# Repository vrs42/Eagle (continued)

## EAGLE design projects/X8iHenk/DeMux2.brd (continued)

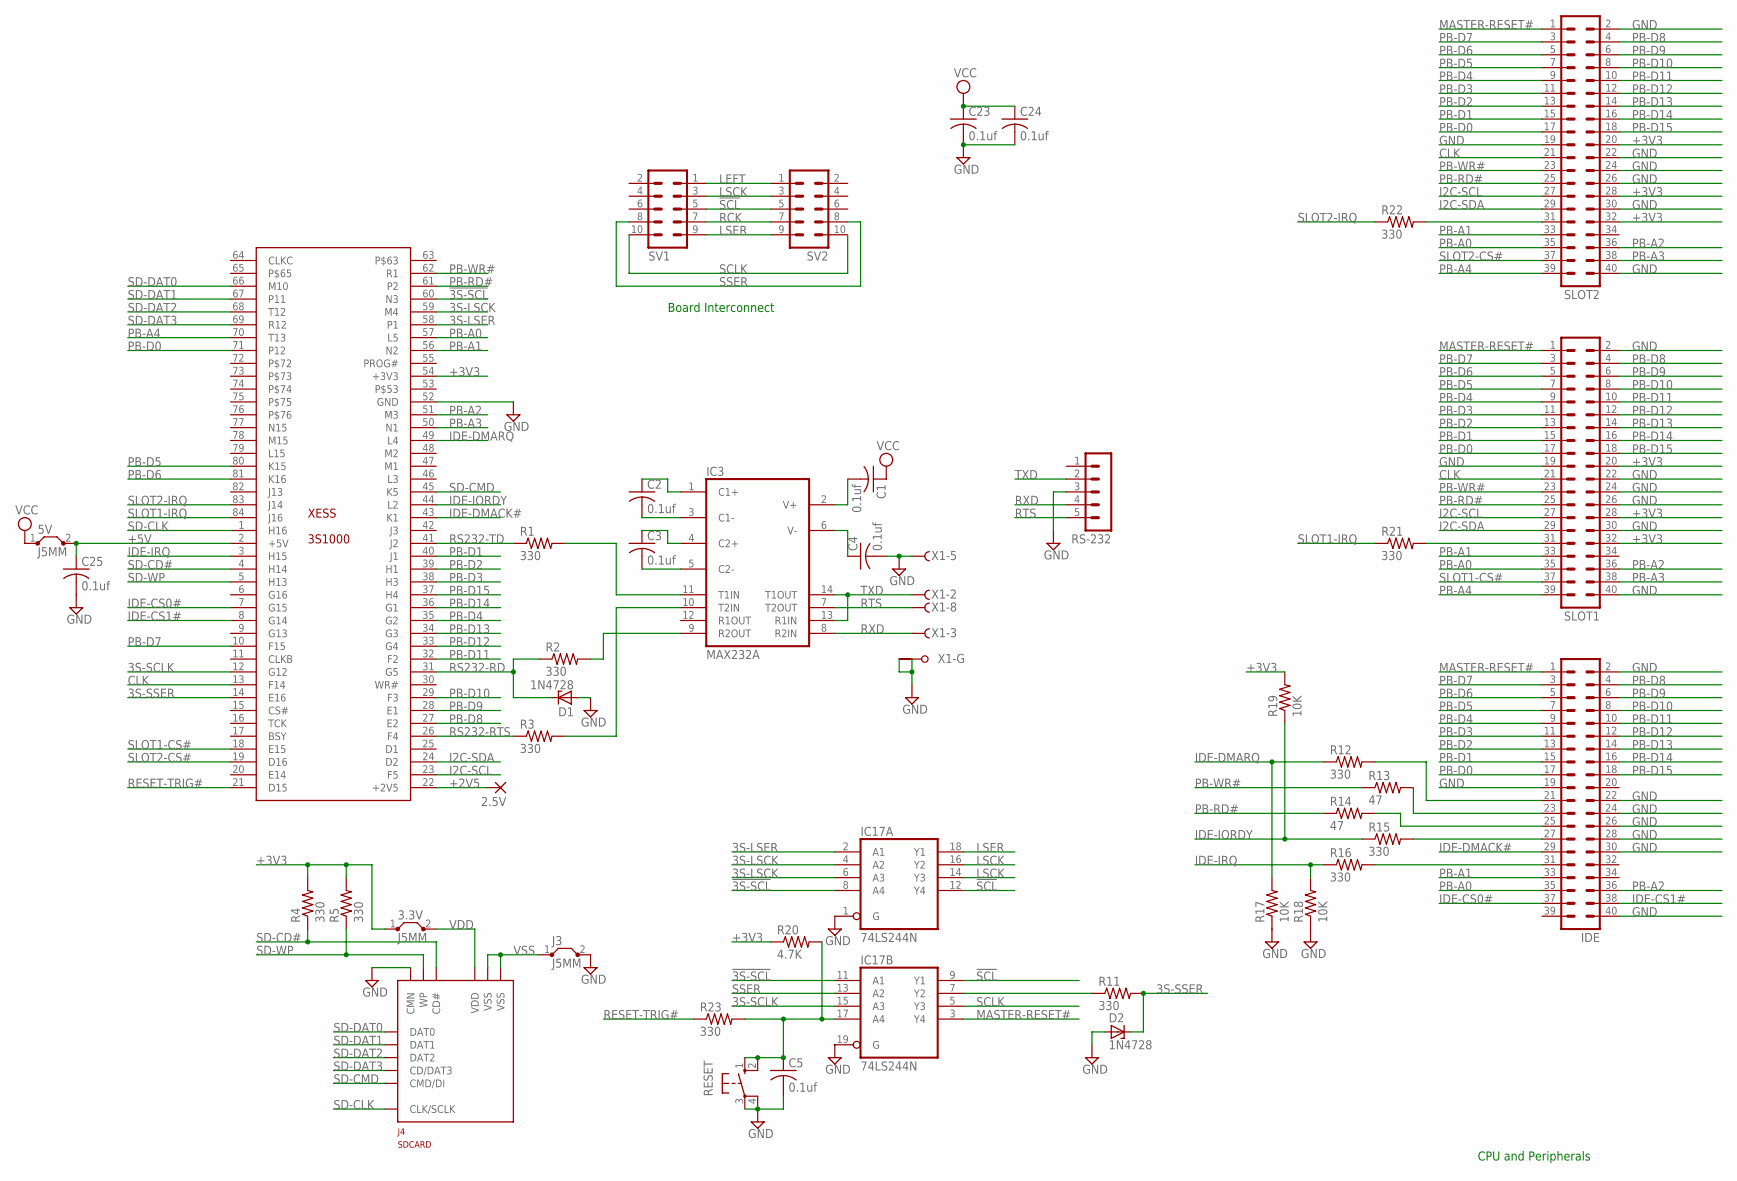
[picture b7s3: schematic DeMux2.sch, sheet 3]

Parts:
2.5V: 1,6/0,8
3.3V, 5V: J5MM; 05
C1, C2, C3, C4, C5, C23, C24, C25: 0.1uf; C050-025X075
D1, D2: 1N4728; DO41Z10
IC3: MAX232A; DIL16
IC17: 74LS244N; DIL20
IDE: MA20-2
J3: J5MM; 05
J4: SDCARD; SCDA5A
R1, R2, R3, R4, R5, R11, R12, R15, R16, R21, R22, R23: 330; 0207/10
R13, R14: 47; 0207/10
R17, R18, R19: 10K; 0207/10
R20: 4.7K; 0207/10
RESET: 40-XX; B3F-40XX
RS-232: MA05-1
SLOT1, SLOT2: MA20-2
SV1, SV2: MA05-2
X1: F09HPS; F09HP
XESS: 3S1000

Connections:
3S-LSCK: IC17.4 (A2), IC17.6 (A3), XESS.59 (M4)
3S-LSER: IC17.2 (A1), XESS.58 (P1)
3S-SCLK: IC17.15 (A3), XESS.12 (G12)
3S-SSER: D2.C, R11.2, XESS.14 (E16)
!3S-SCL: IC17.8 (A4), IC17.11 (A1), XESS.60 (N3)
!SCL: IC17.9 (Y1), IC17.12 (Y4), SV1.5, SV2.5; also elsewhere on the board
+2V5: 2.5V.1, XESS.22 (+2V5)
+3V3: 3.3V.1, R4.2, R5.2, R19.2, R20.1, SLOT1.20, SLOT1.28, SLOT1.32, SLOT2.20, SLOT2.28, SLOT2.32, XESS.54 (+3V3)
+5V: 5V.2, C25.1, XESS.2 (+5V)
CLK: SLOT1.21, SLOT2.21, XESS.13 (F14)
GND: C4.2, C5.2, C23.2, C24.2, C25.2, D1.A, D2.A, IC3.15 (GND), IC17.1 (G), IC17.10 (GND), IC17.19 (G), IDE.2, IDE.19, IDE.22, IDE.24, IDE.26, IDE.28, IDE.30, IDE.40, J3.2, J4.11 (CMN), J4.13 (GND), J4.14 (GND), R17.1, R18.1, RESET.3, RESET.4 (P1), RS-232.3, SLOT1.2, SLOT1.19, SLOT1.22, SLOT1.24, SLOT1.26, SLOT1.30, SLOT1.40, SLOT2.2, SLOT2.19, SLOT2.22, SLOT2.24, SLOT2.26, SLOT2.30, SLOT2.40, X1.5 (F), X1.G1, X1.G2, XESS.52 (GND); also elsewhere on the board
I2C-SCL: SLOT1.27, SLOT2.27, XESS.23 (F5)
I2C-SDA: SLOT1.29, SLOT2.29, XESS.24 (D2)
IDE-CS0#: IDE.37, XESS.7 (G15)
IDE-CS1#: IDE.38, XESS.8 (G14)
IDE-DMACK#: IDE.29, XESS.43 (K1)
IDE-DMARQ: R12.1, R17.2, XESS.49 (L4)
IDE-IORDY: R15.1, R19.1, XESS.44 (L2)
IDE-IRQ: R16.1, R18.2, XESS.3 (H15)
LEFT: SV1.1, SV2.1; also elsewhere on the board
LSCK: IC17.14 (Y3), IC17.16 (Y2), SV1.3, SV2.3; also elsewhere on the board
LSER: IC17.18 (Y1), SV1.9, SV2.9; also elsewhere on the board
MASTER-RESET#: IC17.3 (Y4), IDE.1, SLOT1.1, SLOT2.1
unnamed: IC3.10 (T2IN), R3.2
unnamed: IC3.11 (T1IN), R1.2
unnamed: IC3.9 (R2OUT), R2.2
unnamed: C1.2, IC3.2 (V+)
unnamed: C2.2, IC3.3 (C1-)
unnamed: C2.1, IC3.1 (C1+)
unnamed: C4.1, IC3.6 (V-)
unnamed: C3.1, IC3.4 (C2+)
unnamed: C3.2, IC3.5 (C2-)
unnamed: IC17.7 (Y2), R11.1
unnamed: R21.2, SLOT1.31
unnamed: R22.2, SLOT2.31
unnamed: C5.1, IC17.17 (A4), R20.2, R23.2, RESET.1 (S), RESET.2 (S1)
unnamed: IDE.31, R16.2
unnamed: IDE.27, R15.2
unnamed: IDE.25, R14.2
unnamed: IDE.23, R13.2
unnamed: IDE.21, R12.2
PB-A0: IDE.35, SLOT1.35, SLOT2.35, XESS.57 (L5)
PB-A1: IDE.33, SLOT1.33, SLOT2.33, XESS.56 (N2)
PB-A2: IDE.36, SLOT1.36, SLOT2.36, XESS.51 (M3)
PB-A3: SLOT1.38, SLOT2.38, XESS.50 (N1)
PB-A4: SLOT1.39, SLOT2.39, XESS.70 (T13)
PB-D0: IDE.17, SLOT1.17, SLOT2.17, XESS.71 (P12)
PB-D1: IDE.15, SLOT1.15, SLOT2.15, XESS.40 (J1)
PB-D2: IDE.13, SLOT1.13, SLOT2.13, XESS.39 (H1)
PB-D3: IDE.11, SLOT1.11, SLOT2.11, XESS.38 (H3)
PB-D4: IDE.9, SLOT1.9, SLOT2.9, XESS.35 (G2)
PB-D5: IDE.7, SLOT1.7, SLOT2.7, XESS.80 (K15)
PB-D6: IDE.5, SLOT1.5, SLOT2.5, XESS.81 (K16)
PB-D7: IDE.3, SLOT1.3, SLOT2.3, XESS.10 (F15)
PB-D8: IDE.4, SLOT1.4, SLOT2.4, XESS.27 (E2)
PB-D9: IDE.6, SLOT1.6, SLOT2.6, XESS.28 (E1)
PB-D10: IDE.8, SLOT1.8, SLOT2.8, XESS.29 (F3)
PB-D11: IDE.10, SLOT1.10, SLOT2.10, XESS.32 (F2)
PB-D12: IDE.12, SLOT1.12, SLOT2.12, XESS.33 (G4)
PB-D13: IDE.14, SLOT1.14, SLOT2.14, XESS.34 (G3)
PB-D14: IDE.16, SLOT1.16, SLOT2.16, XESS.36 (G1)
PB-D15: IDE.18, SLOT1.18, SLOT2.18, XESS.37 (H4)
PB-RD#: R14.1, SLOT1.25, SLOT2.25, XESS.61 (P2)
PB-WR#: R13.1, SLOT1.23, SLOT2.23, XESS.62 (R1)
RCK: SV1.7, SV2.7; also elsewhere on the board
RESET-TRIG#: R23.1, XESS.21 (D15)
RS232-RD: D1.C, R2.1, XESS.31 (G5)
RS232-RTS: R3.1, XESS.26 (F4)
RS232-TD: R1.1, XESS.41 (J2)
RTS: IC3.7 (T2OUT), RS-232.5, X1.8 (F)
RXD: IC3.8 (R2IN), RS-232.4, X1.3 (F)
SCLK: IC17.5 (Y3), SV1.10, SV2.10; also elsewhere on the board
SD-CD#: J4.10 (CD#), R4.1, XESS.4 (H14)
SD-CLK: J4.5 (CLK/SCLK), XESS.1 (H16)
SD-CMD: J4.2 (CMD/DI), XESS.45 (K5)
SD-DAT0: J4.7 (DAT0), XESS.66 (M10)
SD-DAT1: J4.8 (DAT1), XESS.67 (P11)
SD-DAT2: J4.9 (DAT2), XESS.68 (T12)
SD-DAT3: J4.1 (CD/DAT3), XESS.69 (R12)
SD-WP: J4.12 (WP), R5.1, XESS.5 (H13)
SLOT1-CS#: SLOT1.37, XESS.18 (E15)
SLOT1-IRQ: R21.1, XESS.84 (J16)
SLOT2-CS#: SLOT2.37, XESS.19 (D16)
SLOT2-IRQ: R22.1, XESS.83 (J14)
SSER: IC17.13 (A2), SV1.8, SV2.8; also elsewhere on the board
TXD: IC3.13 (R1IN), IC3.14 (T1OUT), RS-232.2, X1.2 (F)
VCC: 5V.1, C1.1, C23.1, C24.1, IC3.16 (VCC), IC17.20 (VCC); also elsewhere on the board
VDD: 3.3V.2, J4.4 (VDD)
VSS: J3.1, J4.3 (VSS), J4.6 (VSS)

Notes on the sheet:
CPU and Peripherals
Board Interconnect

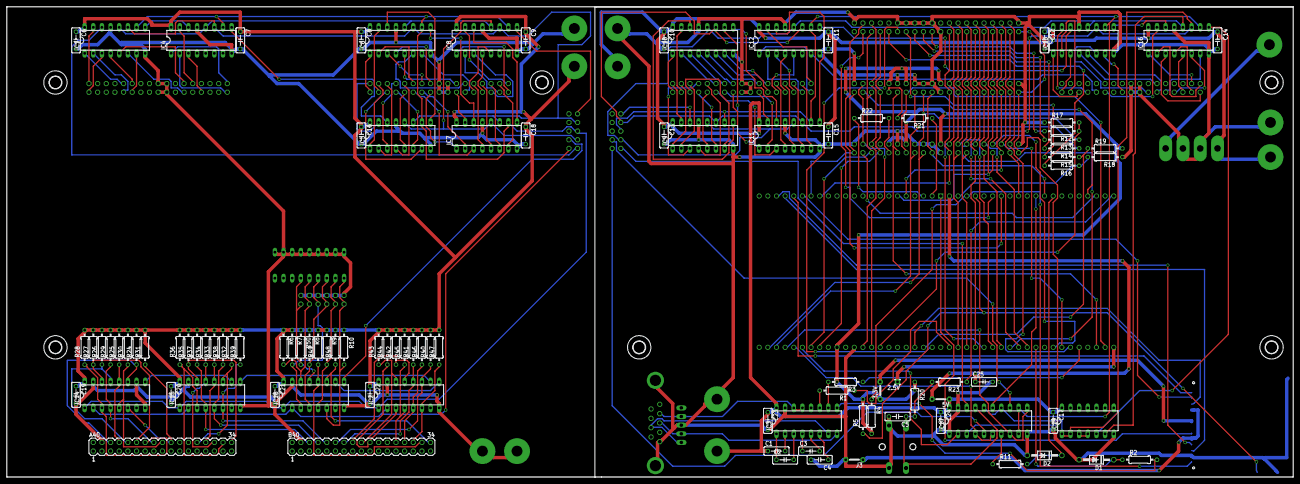
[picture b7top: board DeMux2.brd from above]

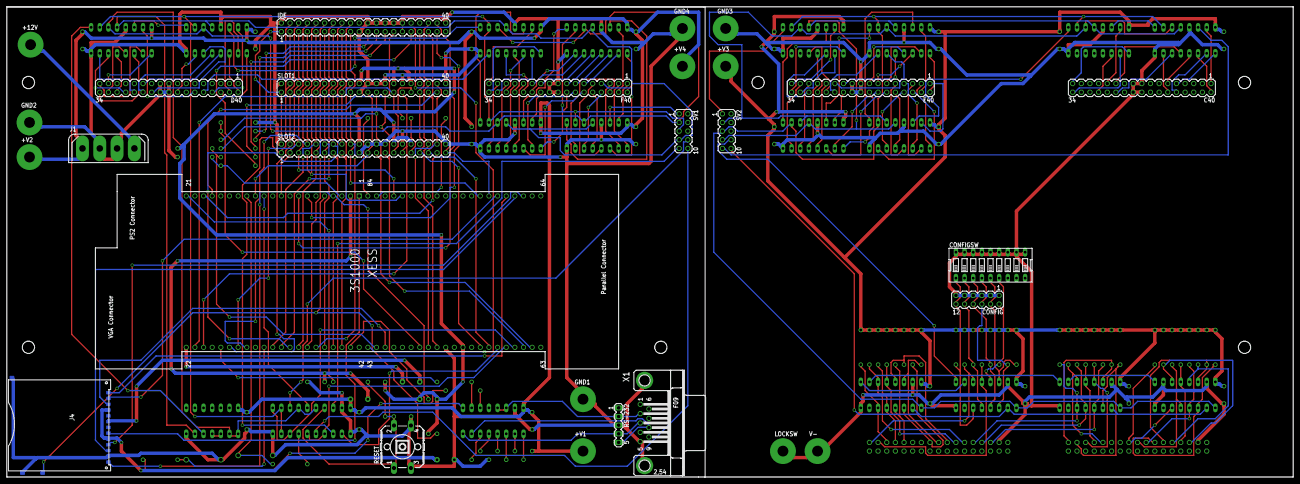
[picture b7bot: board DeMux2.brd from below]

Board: 2 copper layers, 377.8 x 138.1 mm, 136 parts (28 on the bottom side), 226 nets.

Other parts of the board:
U$5, U$6, U$7, U$8, U$9, U$11: 3,6
